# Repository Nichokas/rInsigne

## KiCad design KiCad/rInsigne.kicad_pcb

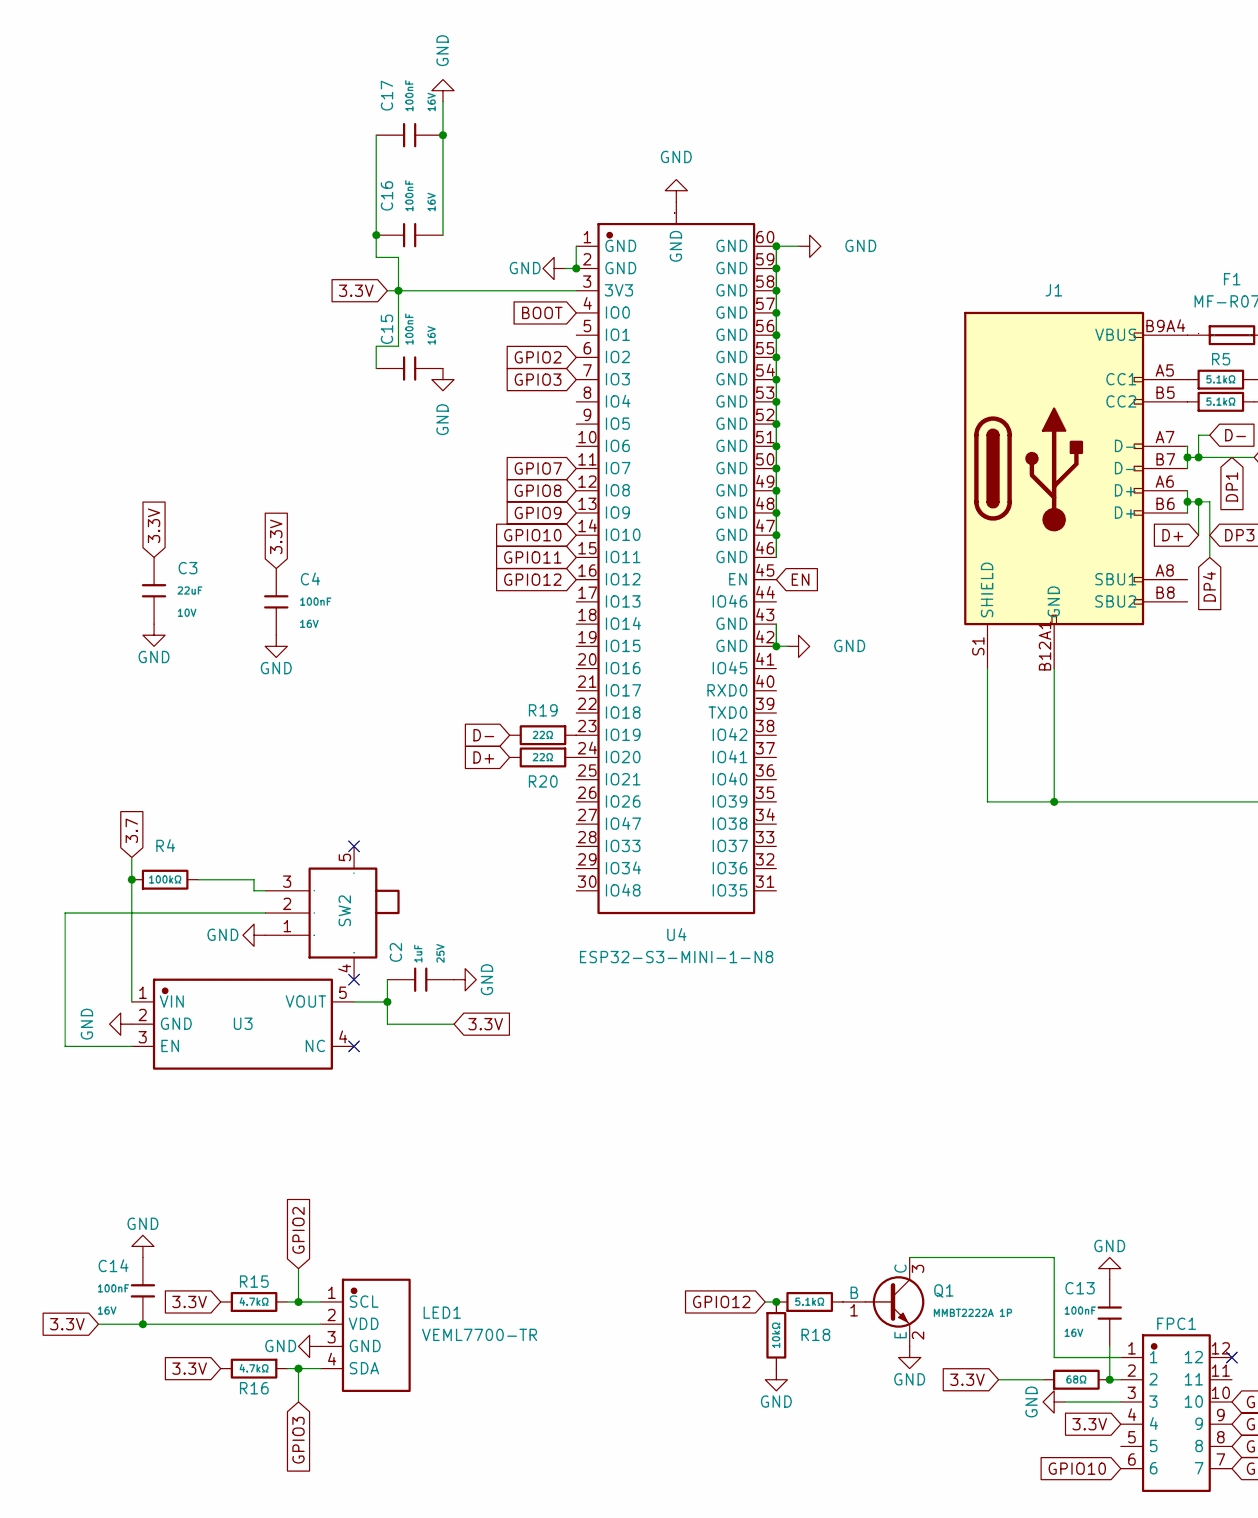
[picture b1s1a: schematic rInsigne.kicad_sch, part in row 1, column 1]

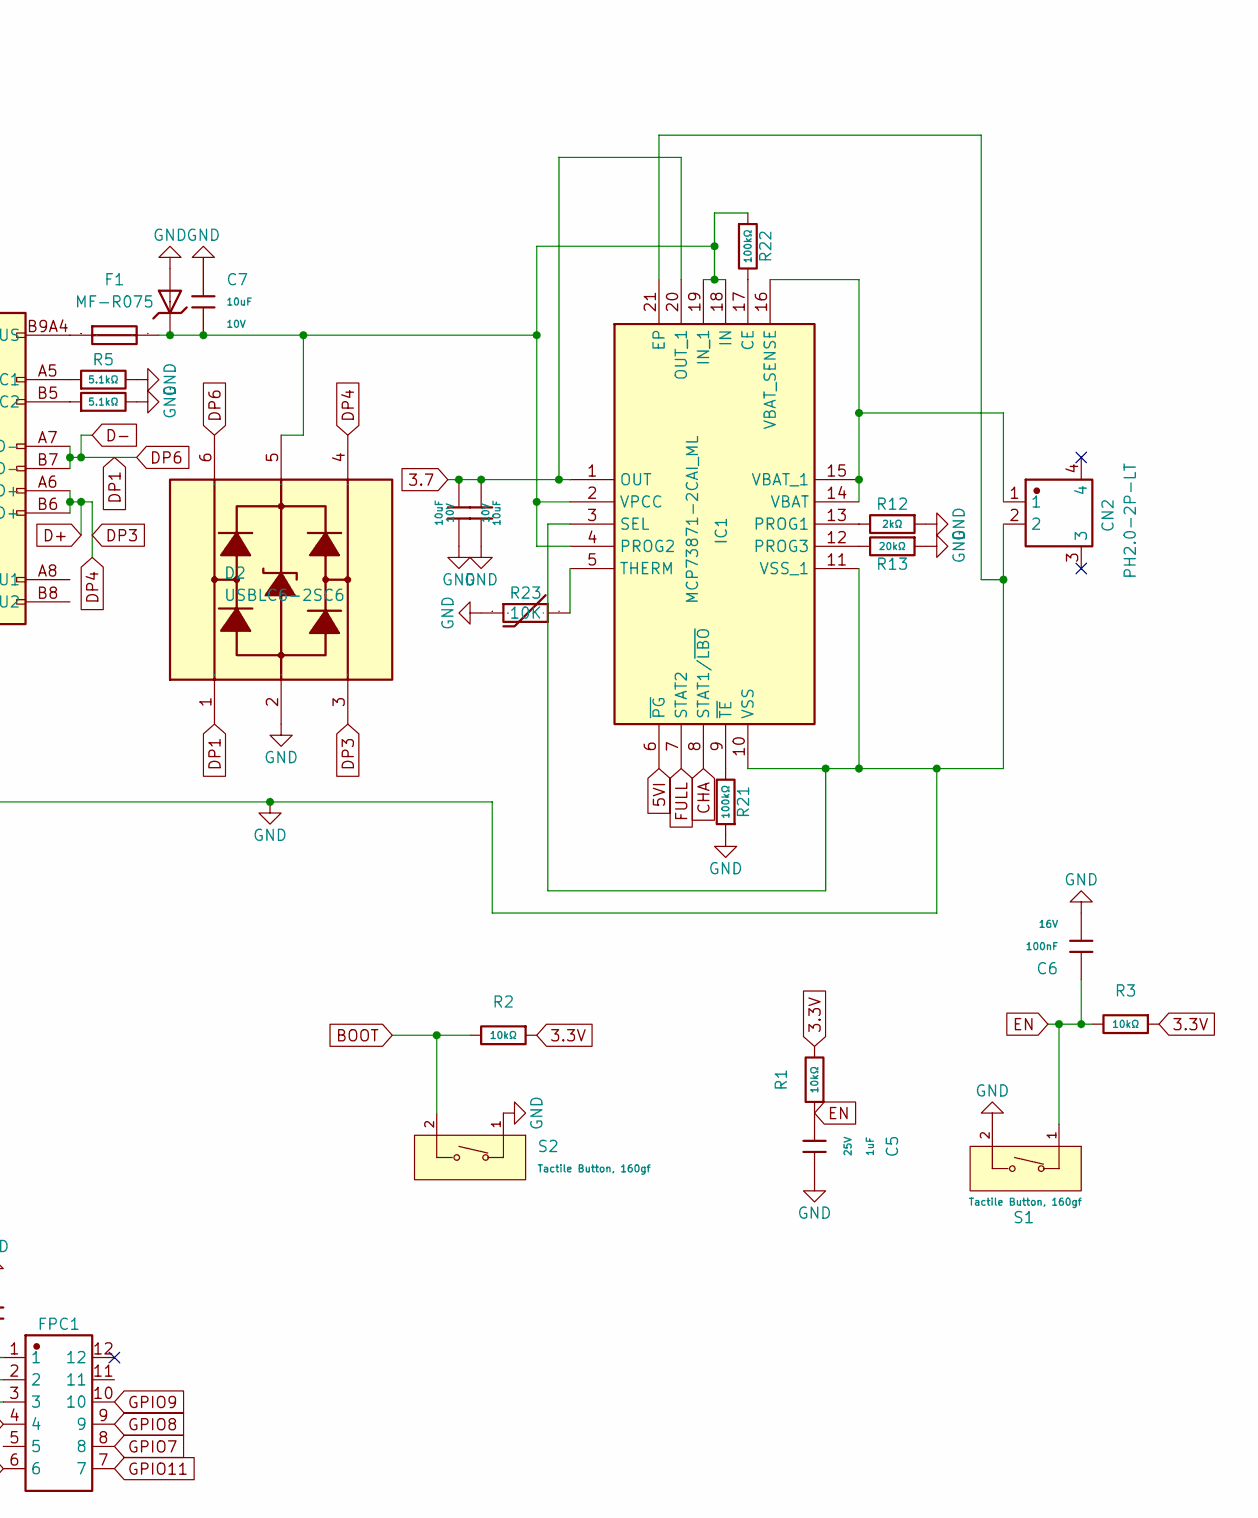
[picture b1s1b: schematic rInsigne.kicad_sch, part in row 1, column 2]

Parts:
C1, C7, C9: 10uF; C_0603; Voltage Rated 10V; Tolerance ±10%; Part CL10A106KP8NNNC; LCSC C19702
C2, C5: 1uF; C_0402; Voltage Rated 25V; Tolerance ±10%; Part CL05A105KA5NQNC; LCSC C52923
C3: 22uF; C_1206; Voltage Rated 10V; Tolerance ±10%; Part CL31A226KPHNNNE; LCSC C5672
C4, C6, C13, C14, C15, C16, C17: 100nF; C_0402; Voltage Rated 16V; Tolerance ±10%; Part CL05B104KO5NNNC; LCSC C1525
CN2: PH2.0-2P-LT; CONN-SMD_PH2.0-1X2PW; Manufacturer Part PH2.0-2P-LT
D1: SMBJ6.0A; D_SMB; Part SMBJ6.0A; LCSC C19077560
D2: USBLC6-2SC6; SOT-23-6_L2.9-W1.6-P0.95-LS2.8-BL; Manufacturer Part USBLC6-2SC6
F1: MF-R075; SMD1812P110TF; Manufacturer Part MF-R075
FPC1: 0.5K-A-10PB; CONN-SMD_0.5K-A-10PB; Manufacturer Part 0.5K-A-10PB
IC1: MCP73871-2CAI_ML; QFN50P400X400X100-21N-D; Manufacturer Part MCP73871-2CAI/ML
J1: Connector, USB-TYPE-C-16P; TYPE-C-SMD_HX-TYPE-C-16PIN; LCSC C2927039
LED1: VEML7700-TR; LED-SMD_4P-L6.8-W2.4_VEML7700-TR; Manufacturer Part VEML7700-TR
Q1: MMBT2222A 1P; Q_SOT-23; Part MMBT2222A 1P; LCSC C8512
R1, R2, R3, R18: 10kΩ; R_0402; Overload Voltage (Max) 50V; Tolerance ±1%; Part 0402WGF1002TCE; LCSC C25744
R4, R21, R22: 100kΩ; R_0402; Overload Voltage (Max) 50V; Tolerance ±1%; Part 0402WGF1003TCE; LCSC C25741
R5, R6, R17: 5.1kΩ; R_0402; Overload Voltage (Max) 50V; Tolerance ±1%; Part 0402WGF5101TCE; LCSC C25905
R12: 2kΩ; R_0402; Overload Voltage (Max) 50V; Tolerance ±1%; Part 0402WGF2001TCE; LCSC C4109
R13: 20kΩ; R_0402; Overload Voltage (Max) 50V; Tolerance ±1%; Part 0402WGF2002TCE; LCSC C25765
R14: 68Ω; R_0603; Overload Voltage (Max) 75V; Tolerance ±1%; Part 0603WAF680JT5E; LCSC C27592
R15, R16: 4.7kΩ; R_0402; Overload Voltage (Max) 50V; Tolerance ±1%; Part 0402WGF4701TCE; LCSC C25900
R19, R20: 22Ω; R_0402; Overload Voltage (Max) 50V; Tolerance ±1%; Part 0402WGF220JTCE; LCSC C25092
R23: 10K; NCP15XH103F03RC; Manufacturer Part NCP15XH103F03RC
S1, S2: Tactile Button, 160gf; SW_TS-1088-AR02016; Voltage Rating (Dc) 12V; Part TS-1088-AR02016; LCSC C720477
SW2: MINI MSK12CO2; SW-SMD_MSK12CO2; Manufacturer Part MINI MSK12CO2
U3: AP2112K-3.3TRG1; SOT-25-5_L2.9-W1.6-P0.95-LS2.8-BL; Manufacturer Part AP2112K-3.3TRG1
U4: ESP32-S3-MINI-1-N8; BULETM-SMD_ESP32-S3-MINI-1-N8; Manufacturer Part ESP32-S3-MINI-1-N8

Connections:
3.3V: C2.1, C3.1, C4.1, C14.2, C15.1, C16.1, C17.1, FPC1.4, LED1.2 (VDD), R1.2, R2.1, R3.1, R14.1, R15.1, R16.2, U3.5 (VOUT), U4.3 (3V3)
3.7: C1.2, C9.2, IC1.1 (OUT), IC1.20 (OUT_1), R4.1, U3.1 (VIN)
5VI: IC1.6 (~PG)
BOOT: R2.2, S2.2 (B), U4.4 (IO0)
CHA: IC1.8 (STAT1/~LBO)
D+: D2.3, D2.4, J1.A6 (D+), J1.B6 (D+), R20.2
D-: D2.1, D2.6, J1.A7 (D-), J1.B7 (D-), R19.2
EN: C5.1, C6.1, R1.1, R3.2, S1.1 (A), U4.45 (EN)
FULL: IC1.7 (STAT2)
GND: C1.1, C2.2, C3.2, C4.2, C5.2, C6.2, C7.2, C9.1, C13.1, C14.1, C15.2, C16.2, C17.2, CN2.2, D1.2, D2.2, FPC1.3, IC1.3 (SEL), IC1.10 (VSS), IC1.11 (VSS_1), IC1.21 (EP), J1.A12B1 (GND), J1.B12A1 (GND), J1.S1 (SHIELD), LED1.3 (GND), Q1.2 (E), R5.2, R6.2, R12.1, R13.1, R18.2, R21.1, R23.1, S1.2 (B), S2.1 (A), SW2.1, U3.2 (GND), U4.1 (GND), U4.2 (GND), U4.42 (GND), U4.43 (GND), U4.46 (GND), U4.47 (GND), U4.48 (GND), U4.49 (GND), U4.50 (GND), U4.51 (GND), U4.52 (GND), U4.53 (GND), U4.54 (GND), U4.55 (GND), U4.56 (GND), U4.57 (GND), U4.58 (GND), U4.59 (GND), U4.60 (GND), U4.GND
GPIO2: LED1.1 (SCL), R15.2, U4.6 (IO2)
GPIO3: LED1.4 (SDA), R16.1, U4.7 (IO3)
GPIO7: FPC1.8, U4.11 (IO7)
GPIO8: FPC1.9, U4.12 (IO8)
GPIO9: FPC1.10, U4.13 (IO9)
GPIO10: FPC1.6, U4.14 (IO10)
GPIO11: FPC1.7, U4.15 (IO11)
GPIO12: R17.1, R18.1, U4.16 (IO12)
unnamed: C13.2, FPC1.2, R14.2
unnamed: F1.1, J1.A9B4 (VBUS), J1.B9A4 (VBUS)
unnamed: IC1.17 (CE), R22.2
unnamed: C7.1, D1.1, D2.5, F1.2, IC1.2 (VPCC), IC1.4 (PROG2), IC1.18 (IN), IC1.19 (IN_1), R22.1
unnamed: IC1.13 (PROG1), R12.2
unnamed: IC1.12 (PROG3), R13.2
unnamed: IC1.5 (THERM), R23.2
unnamed: CN2.1, IC1.14 (VBAT), IC1.15 (VBAT_1), IC1.16 (VBAT_SENSE)
unnamed: IC1.9 (~TE), R21.2
unnamed: J1.A5 (CC1), R5.1
unnamed: J1.B5 (CC2), R6.1
unnamed: Q1.1 (B), R17.2
unnamed: FPC1.1, Q1.3 (C)
unnamed: R4.2, SW2.3
unnamed: SW2.2, U3.3 (EN)
unnamed: R19.1, U4.23 (IO19)
unnamed: R20.1, U4.24 (IO20)

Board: 2 copper layers, 45 parts (23 on the bottom side), 32 nets, no tracks yet.

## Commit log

2025-11-08 Schematic (almost) finished
2025-11-08 LICENSE
2025-11-09 Updated the Battery driver to its JLCPCB version
2025-11-09 fitted all components into the perimeter of the badge
